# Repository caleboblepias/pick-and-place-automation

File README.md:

# pick-and-place-automation
This project implements the embedded control backbone of an automated pick and place machine. The system centers on a custom STM32F103RB-based PCB running bare-metal firmware for precise motion control of stepper and servo actuators.

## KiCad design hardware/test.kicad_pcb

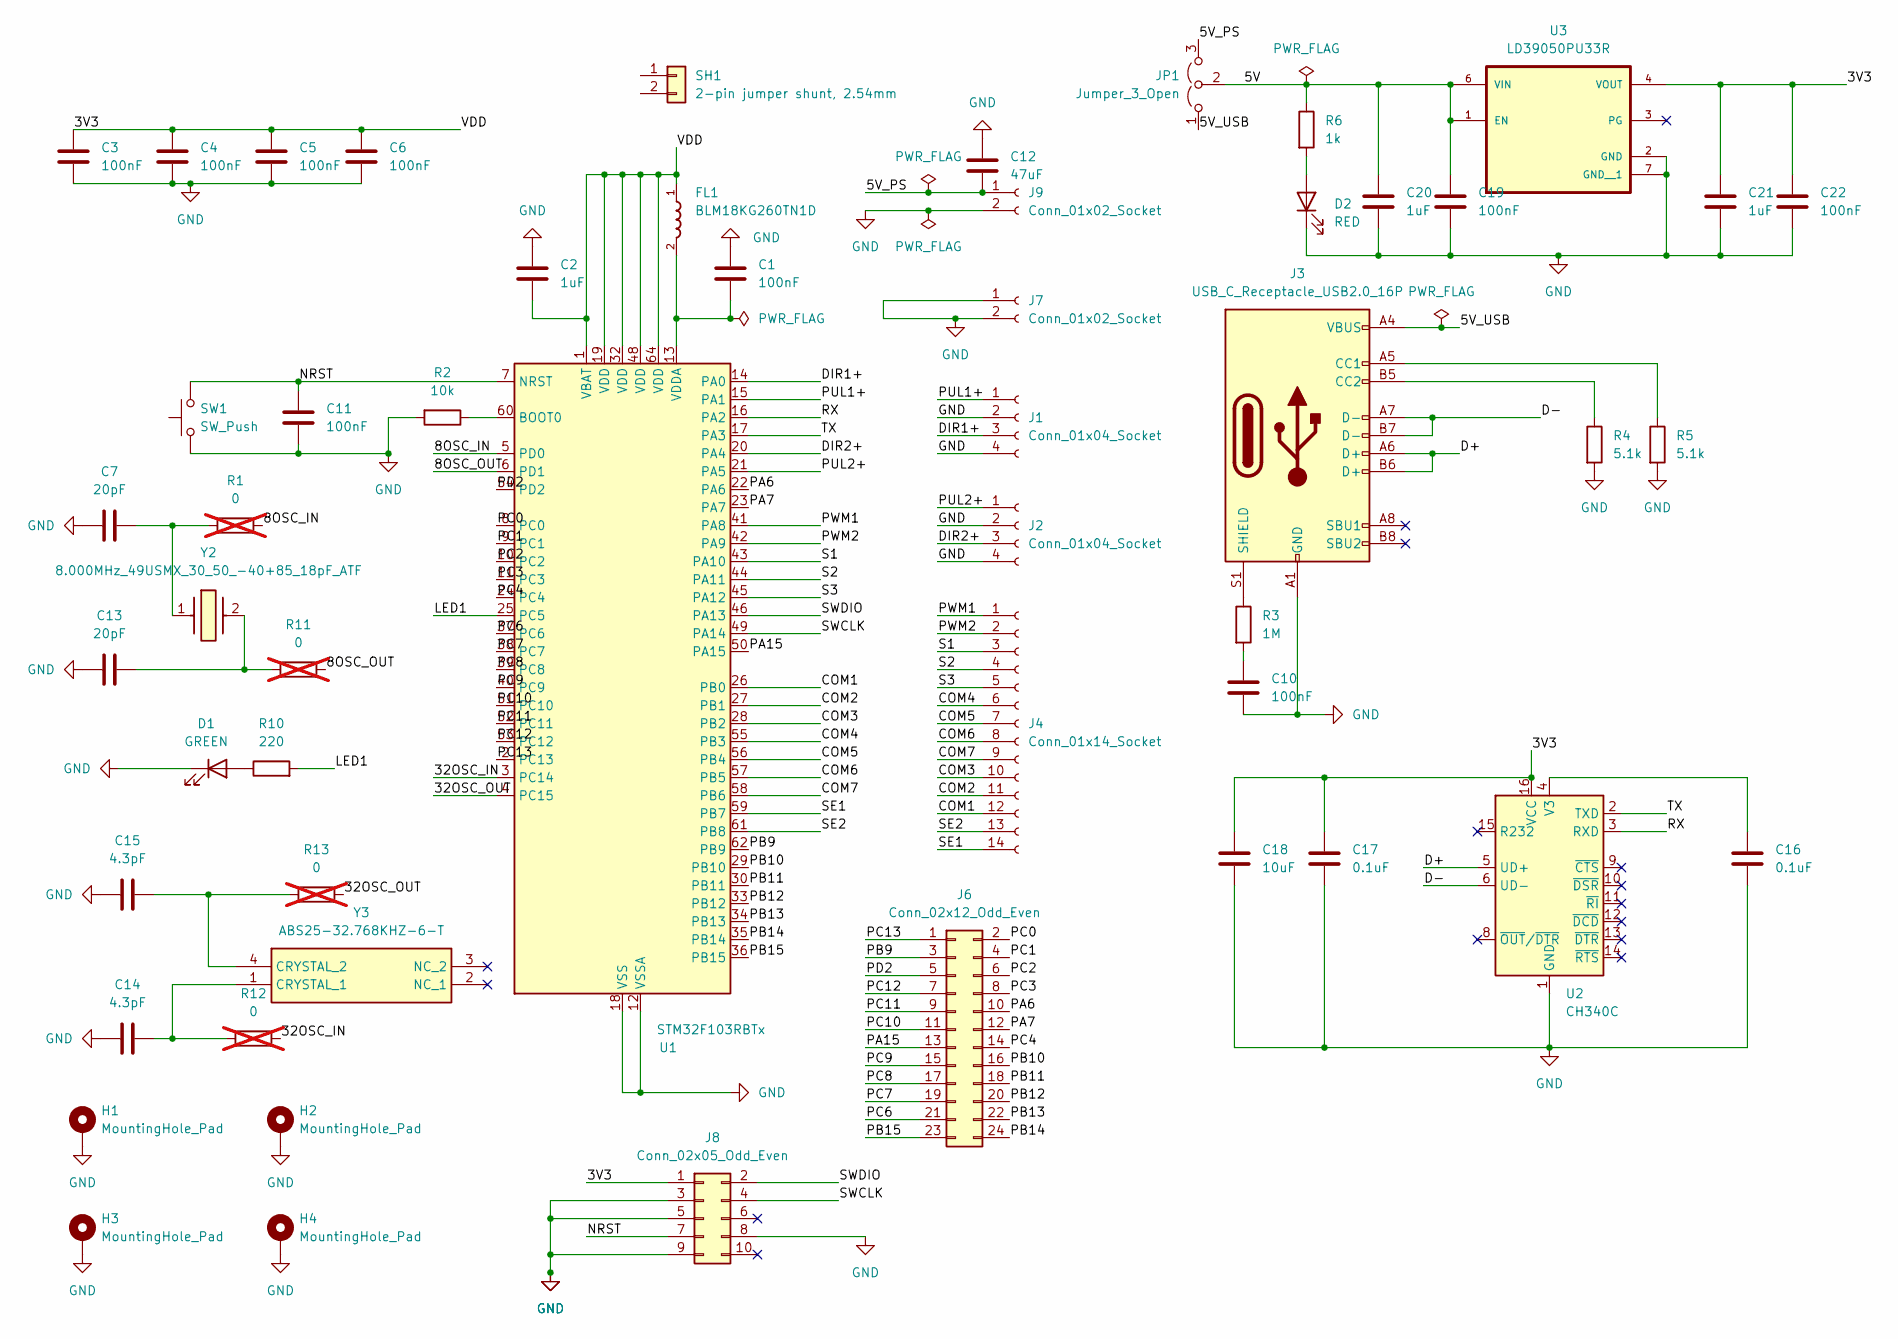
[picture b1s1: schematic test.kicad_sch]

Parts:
C1, C3, C4, C5, C6, C10, C11, C19, C22: 100nF; C_0603_1608Metric
C2, C20, C21: 1uF; C_0603_1608Metric
C7, C13: 20pF; C_0603_1608Metric
C12: 47uF; C_1210_3225Metric
C14, C15: 4.3pF; C_0603_1608Metric
C16, C17: 0.1uF; C_0603_1608Metric
C18: 10uF; C_0603_1608Metric
D1: GREEN; LED_0603_1608Metric
D2: RED; LED_0603_1608Metric
FL1: BLM18KG260TN1D; BEADC1608X75N
H1, H2, H3, H4: MountingHole_Pad; MountingHole_3.2mm_M3_Pad
J1, J2: Conn_01x04_Socket; PhoenixContact_MC_1,5_4-G-3.5_1x04_P3.50mm_Horizontal
J3: USB_C_Receptacle_USB2.0_16P; USB_C_Receptacle_HRO_TYPE-C-31-M-12
J4: Conn_01x14_Socket; PhoenixContact_MC_1,5_14-G-3.5_1x14_P3.50mm_Horizontal
J6: Conn_02x12_Odd_Even; PinHeader_2x12_P2.54mm_Vertical
J7, J9: Conn_01x02_Socket; PhoenixContact_MC_1,5_2-G-3.5_1x02_P3.50mm_Horizontal
J8: Conn_02x05_Odd_Even; PinHeader_2x05_P2.54mm_Vertical
JP1: Jumper_3_Open; PinHeader_1x03_P2.54mm_Vertical
R1, R11, R12, R13: 0; R_0603_1608Metric; not fitted
R2: 10k; R_0603_1608Metric
R3: 1M; R_0603_1608Metric
R4, R5: 5.1k; R_0603_1608Metric
R6: 1k; R_0603_1608Metric
R10: 220; R_0603_1608Metric
SH1: 2-pin jumper shunt, 2.54mm
SW1: SW_Push; SW_SPST_TL3342
U1: STM32F103RBTx; LQFP-64_10x10mm_P0.5mm
U2: CH340C; SOIC-16_3.9x9.9mm_P1.27mm
U3: LD39050PU33R; SON95P300X300X100-7N; DIGI-KEY_PART_NUMBER 497-8716-1-ND
Y2: 8.000MHz_49USMX_30_50_-40+85_18pF_ATF; 8000MHz49USMX3050408518pFATF; Manufacturer_Part_Number 8.000MHz 49USMX/30/50/-40+85/18pF/ATF
Y3: ABS25-32.768KHZ-6-T; ABS2532768KHZT; Manufacturer_Part_Number ABS25-32.768KHZ-6-T

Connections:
/3V3: C2.2, C3.1, C4.1, C5.1, C6.1, C17.1, C18.1, C21.1, C22.1, FL1.1, J8.1, U1.1 (VBAT), U1.19 (VDD), U1.32 (VDD), U1.48 (VDD), U1.64 (VDD), U2.16 (VCC), U3.4 (VOUT)
/5V: C19.1, C20.1, JP1.2 (C), R6.1, U3.1 (EN), U3.6 (VIN)
/5V_PS: C12.2, J9.1, JP1.3 (B)
/5V_USB: J3.A4 (VBUS), J3.A9 (VBUS), J3.B4 (VBUS), J3.B9 (VBUS), JP1.1 (A)
/8OSC_IN: R1.2, U1.5 (PD0)
/8OSC_OUT: R11.2, U1.6 (PD1)
/32OSC_IN: R12.2, U1.3 (PC14)
/32OSC_OUT: R13.2, U1.4 (PC15)
/COM1: J4.12, U1.26 (PB0)
/COM2: J4.11, U1.27 (PB1)
/COM3: J4.10, U1.28 (PB2)
/COM4: J4.6, U1.55 (PB3)
/COM5: J4.7, U1.56 (PB4)
/COM6: J4.8, U1.57 (PB5)
/COM7: J4.9, U1.58 (PB6)
/D+: J3.A6 (D+), J3.B6 (D+), U2.5 (UD+)
/D-: J3.A7 (D-), J3.B7 (D-), U2.6 (UD-)
/DIR1+: J1.3, U1.14 (PA0)
/DIR2+: J2.3, U1.20 (PA4)
/LED1: R10.2, U1.25 (PC5)
/NRST: C11.1, J8.7, SW1.2, U1.7 (NRST)
/PA6: J6.10, U1.22 (PA6)
/PA7: J6.12, U1.23 (PA7)
/PA15: J6.13, U1.50 (PA15)
/PB9: J6.3, U1.62 (PB9)
/PB10: J6.16, U1.29 (PB10)
/PB11: J6.18, U1.30 (PB11)
/PB12: J6.20, U1.33 (PB12)
/PB13: J6.22, U1.34 (PB13)
/PB14: J6.24, U1.35 (PB14)
/PB15: J6.23, U1.36 (PB15)
/PC0: J6.2, U1.8 (PC0)
/PC1: J6.4, U1.9 (PC1)
/PC2: J6.6, U1.10 (PC2)
/PC3: J6.8, U1.11 (PC3)
/PC4: J6.14, U1.24 (PC4)
/PC6: J6.21, U1.37 (PC6)
/PC7: J6.19, U1.38 (PC7)
/PC8: J6.17, U1.39 (PC8)
/PC9: J6.15, U1.40 (PC9)
/PC10: J6.11, U1.51 (PC10)
/PC11: J6.9, U1.52 (PC11)
/PC12: J6.7, U1.53 (PC12)
/PC13: J6.1, U1.2 (PC13)
/PD2: J6.5, U1.54 (PD2)
/PUL1+: J1.1, U1.15 (PA1)
/PUL2+: J2.1, U1.21 (PA5)
/PWM1: J4.1, U1.41 (PA8)
/PWM2: J4.2, U1.42 (PA9)
/RX: U1.16 (PA2), U2.3 (RXD)
/S1: J4.3, U1.43 (PA10)
/S2: J4.4, U1.44 (PA11)
/S3: J4.5, U1.45 (PA12)
/SE1: J4.14, U1.59 (PB7)
/SE2: J4.13, U1.61 (PB8)
/SWCLK: J8.4, U1.49 (PA14)
/SWDIO: J8.2, U1.46 (PA13)
/TX: U1.17 (PA3), U2.2 (TXD)
GND: C1.1, C2.1, C3.2, C4.2, C5.2, C6.2, C7.1, C10.2, C11.2, C12.1, C13.2, C14.1, C15.2, C16.2, C17.2, C18.2, C19.2, C20.2, C21.2, C22.2, D1.1 (K), D2.1 (K), H1.1, H2.1, H3.1, H4.1, J1.2, J1.4, J2.2, J2.4, J3.A1 (GND), J3.A12 (GND), J3.B1 (GND), J3.B12 (GND), J7.1, J7.2, J8.3, J8.5, J8.8, J8.9, J9.2, R2.2, R4.2, R5.2, SW1.1, U1.12 (VSSA), U1.18 (VSS), U1.31 (VSS), U1.47 (VSS), U1.63 (VSS), U2.1 (GND), U3.2 (GND), U3.7 (GND__1)
unnamed: C7.2, R1.1, Y2.1
unnamed: C10.1, R3.2
unnamed: C13.1, R11.1, Y2.2
unnamed: D1.2 (A), R10.1
unnamed: D2.2 (A), R6.2
unnamed: J3.A5 (CC1), R5.1
unnamed: J3.B5 (CC2), R4.1
unnamed: J3.S1 (SHIELD), R3.1
unnamed: R2.1, U1.60 (BOOT0)
unnamed: C1.2, FL1.2, U1.13 (VDDA)
unnamed: C16.1, U2.4 (V3)
unnamed: C14.2, R12.1, Y3.1 (CRYSTAL_1)
unnamed: C15.1, R13.1, Y3.4 (CRYSTAL_2)

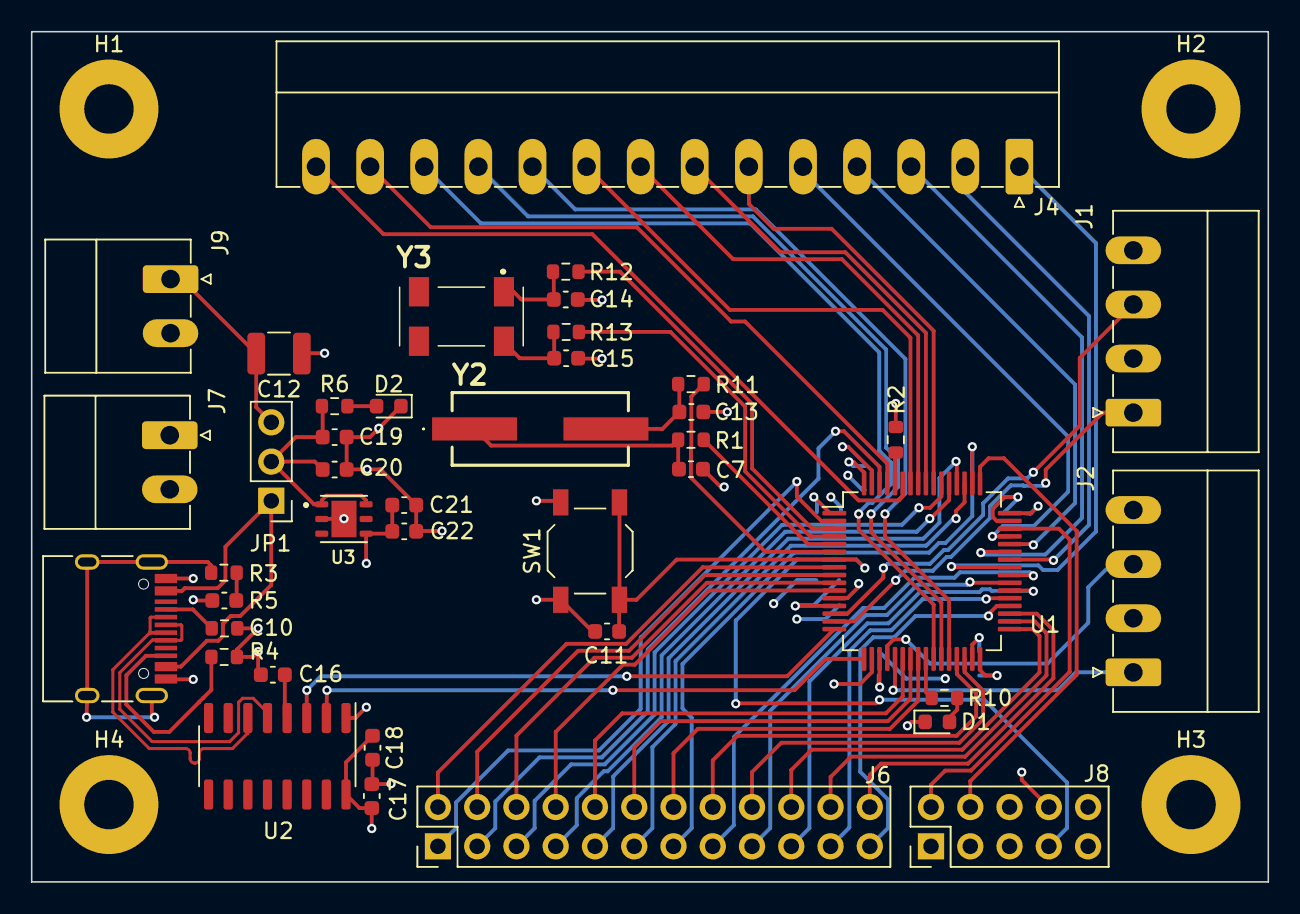
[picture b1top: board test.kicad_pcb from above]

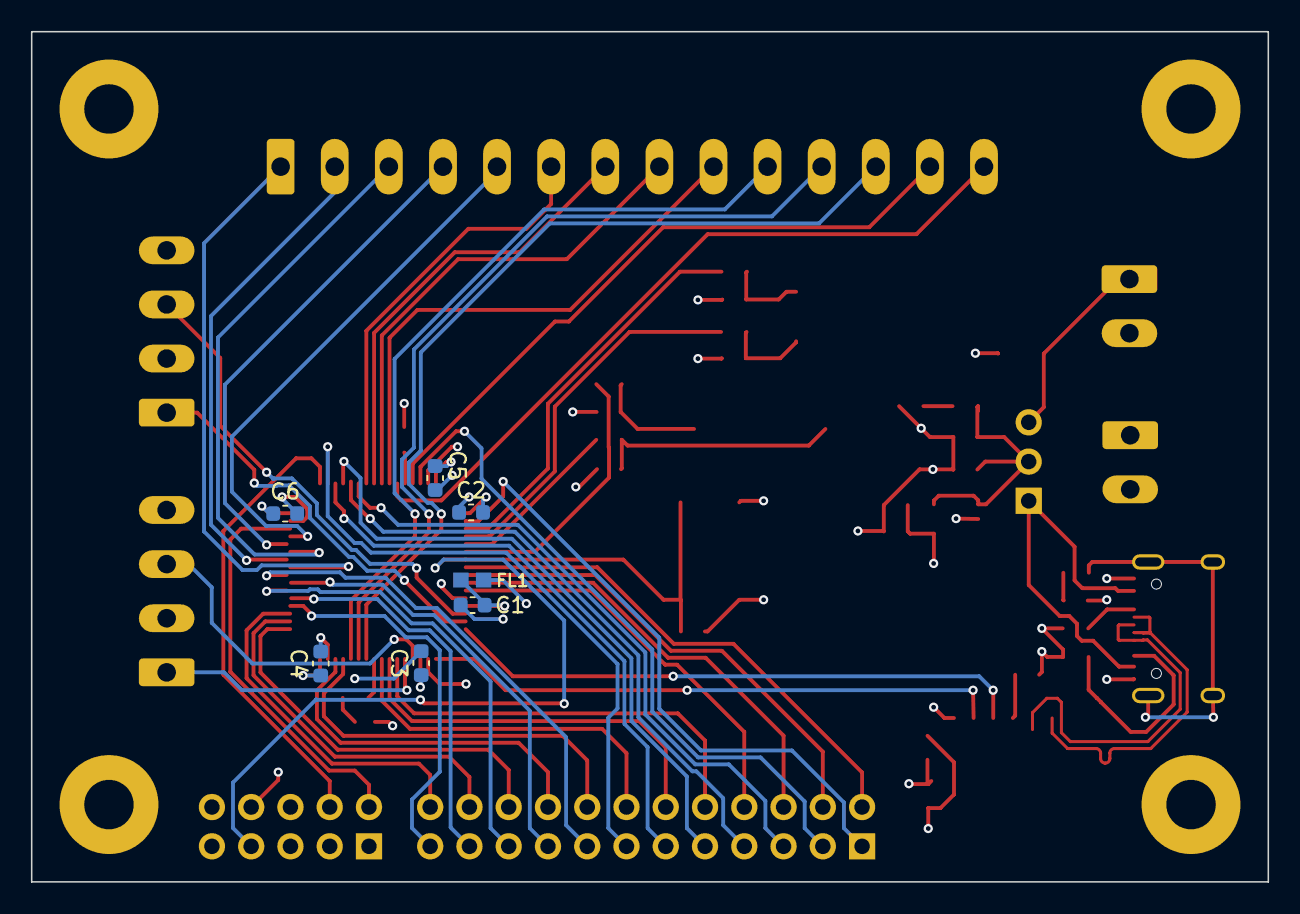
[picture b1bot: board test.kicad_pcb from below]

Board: 4 copper layers, 80.0 x 55.0 mm, 52 parts (7 on the bottom side), 72 nets.

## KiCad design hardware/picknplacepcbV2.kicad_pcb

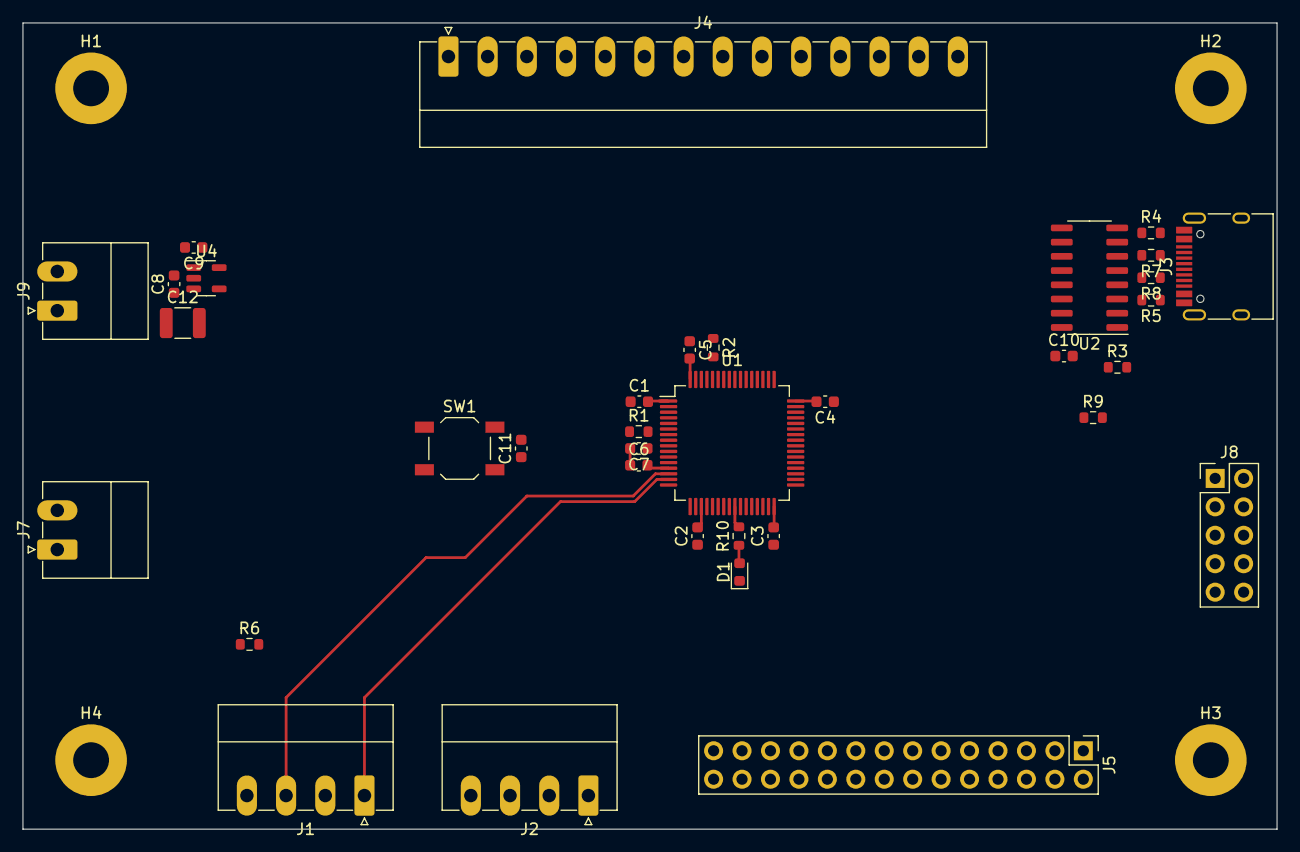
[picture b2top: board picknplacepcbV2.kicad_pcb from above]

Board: 2 copper layers, 112.0 x 72.0 mm, 39 parts (0 on the bottom side), 68 nets.

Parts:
C1, C2, C3, C4, C5, C6: 0.1uF; C_0603_1608Metric
C7, C8, C9: 1uF; C_0603_1608Metric
C10, C11: 100nF; C_0603_1608Metric
C12: 47uF; C_1210_3225Metric
D1: LED; LED_0603_1608Metric
H1, H2, H3, H4: MountingHole_Pad; MountingHole_3.2mm_M3_Pad
J1, J2: Conn_01x04_Socket; PhoenixContact_MC_1,5_4-G-3.5_1x04_P3.50mm_Horizontal
J3: USB_C_Receptacle_USB2.0_16P; USB_C_Receptacle_HRO_TYPE-C-31-M-12
J4: Conn_01x14_Socket; PhoenixContact_MC_1,5_14-G-3.5_1x14_P3.50mm_Horizontal
J5: Conn_02x14_Odd_Even; PinHeader_2x14_P2.54mm_Vertical
J7, J9: Conn_01x02_Socket; PhoenixContact_MC_1,5_2-G-3.5_1x02_P3.50mm_Horizontal
J8: Conn_02x05_Odd_Even; PinHeader_2x05_P2.54mm_Vertical
R1, R2: 10k; R_0603_1608Metric
R3: 1M; R_0603_1608Metric
R4, R5: 5.1k; R_0603_1608Metric
R6: 0; R_0603_1608Metric
R7, R8: 22; R_0603_1608Metric
R9: 100; R_0603_1608Metric
R10: 220; R_0603_1608Metric
SW1: SW_Push; SW_SPST_TL3342
U1: STM32F103RBTx; LQFP-64_10x10mm_P0.5mm
U2: CH340C; SOIC-16_3.9x9.9mm_P1.27mm
U4: AP2112K-3.3; SOT-23-5

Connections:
+5V: C8.1, C12.2, J3.A4 (VBUS), J3.A9 (VBUS), J3.B4 (VBUS), J3.B9 (VBUS), J9.1, U4.1 (VIN), U4.3 (EN)
/+3.3V: C1.2, C2.2, C3.2, C4.2, C5.2, C6.2, C9.1, R1.2, R9.1, U1.1 (VBAT), U1.13 (VDDA), U1.19 (VDD), U1.32 (VDD), U1.48 (VDD), U1.64 (VDD), U2.16 (VCC), U4.5 (VOUT)
/+3.3V_SENSE: J8.1, R9.2
/COM1: J4.3, U1.26 (PB0)
/COM2: J4.4, U1.27 (PB1)
/COM3: J4.5, U1.28 (PB2)
/COM4: J4.6, U1.55 (PB3)
/COM5: J4.7, U1.56 (PB4)
/COM6: J4.8, U1.57 (PB5)
/COM7: J4.9, U1.58 (PB6)
/D+: R8.2, U2.5 (UD+)
/D-: R7.2, U2.6 (UD-)
/DIR1+: J1.3, U1.14 (PA0)
/DIR2+: J2.3, U1.20 (PA4)
/GND_EXT: J7.1, R6.1
/LED1: R10.2, U1.25 (PC5)
/NRST: C11.1, J8.7, R1.1, SW1.2, U1.7 (NRST)
/PA6: J5.10, U1.22 (PA6)
/PA7: J5.12, U1.23 (PA7)
/PA15: J5.14, U1.50 (PA15)
/PB9: J5.16, U1.62 (PB9)
/PB10: J5.18, U1.29 (PB10)
/PB11: J5.20, U1.30 (PB11)
/PB12: J5.22, U1.33 (PB12)
/PB13: J5.24, U1.34 (PB13)
/PB14: J5.26, U1.35 (PB14)
/PB15: J5.28, U1.36 (PB15)
/PC0: J5.7, U1.8 (PC0)
/PC1: J5.9, U1.9 (PC1)
/PC2: J5.11, U1.10 (PC2)
/PC3: J5.13, U1.11 (PC3)
/PC4: J5.15, U1.24 (PC4)
/PC6: J5.17, U1.37 (PC6)
/PC7: J5.19, U1.38 (PC7)
/PC8: J5.21, U1.39 (PC8)
/PC9: J5.23, U1.40 (PC9)
/PC10: J5.25, U1.51 (PC10)
/PC11: J5.27, U1.52 (PC11)
/PC12: J5.2, U1.53 (PC12)
/PC13: J5.4, U1.2 (PC13)
/PC14: J5.6, U1.3 (PC14)
/PC15: J5.8, U1.4 (PC15)
/PD0: J5.1, U1.5 (PD0)
/PD1: J5.3, U1.6 (PD1)
/PD2: J5.5, U1.54 (PD2)
/PUL1+: J1.1, U1.15 (PA1)
/PUL2+: J2.1, U1.21 (PA5)
/PWM1: J4.1, U1.41 (PA8)
/PWM2: J4.2, U1.42 (PA9)
/RX: U1.16 (PA2), U2.3 (RXD)
/S1: J4.10, U1.43 (PA10)
/S2: J4.11, U1.44 (PA11)
/S3: J4.12, U1.45 (PA12)
/SE1: J4.13, U1.59 (PB7)
/SE2: J4.14, U1.61 (PB8)
/SWCLK: J8.4, U1.49 (PA14)
/SWDIO: J8.2, U1.46 (PA13)
/TX: U1.17 (PA3), U2.2 (TXD)
GND: C1.1, C2.1, C3.1, C4.1, C5.1, C7.1, C8.2, C9.2, C10.2, C11.2, C12.1, D1.1 (K), H1.1, H2.1, H3.1, H4.1, J1.2, J1.4, J2.2, J2.4, J3.A1 (GND), J3.A12 (GND), J3.B1 (GND), J3.B12 (GND), J7.2, J8.3, J8.5, J8.8, J8.9, J9.2, R2.1, R4.2, R5.2, R6.2, SW1.1, U1.12 (VSSA), U1.18 (VSS), U1.31 (VSS), U1.47 (VSS), U1.63 (VSS), U2.1 (GND), U4.2 (GND)
unnamed: C6.1, C7.2
unnamed: C10.1, R3.2
unnamed: D1.2 (A), R10.1
unnamed: J3.A5 (CC1), R5.1
unnamed: J3.B5 (CC2), R4.1
unnamed: J3.A6 (D+), J3.B6 (D+), R8.1
unnamed: J3.A7 (D-), J3.B7 (D-), R7.1
unnamed: J3.S1 (SHIELD), R3.1
unnamed: R2.2, U1.60 (BOOT0)

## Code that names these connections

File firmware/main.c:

#include <stdint.h>     // Brings in fixed-width types: uint8_t, uint16_t, etc.
#include "stm32f10x.h"
#include "uart.h"
#include "stepper.h"
#include "gpio.h"
#include "servo.h"
#include "system.h"
#include "calibrate.h"
#include "limit.h"

int main(void)
{
	set_system_state(IDLE);
	USART2_init();
	
	limit_init(0); // Y top limit at PB0
	limit_init(1); // Y bottom limit at PB1
	limit_init(2); // Z top limit at PB2
	limit_init(3); // Z bottom limit at PB3
	
	
	pulse_width_init();
	
	stepper1_init();
	stepper2_init();
	
	set_stepper1_step_freq(6400);
	set_stepper2_step_freq(6400);
	
	set_stepper1_dir(1);
	set_stepper2_dir(0);
	
	//drive_stepper1(800);
	//drive_stepper2(800);
	//calibrate();
	
	servo1_init();
	set_servo1_angle(135);
	/*
	for (uint32_t i = 0; i < 8000; i++) {}
	set_servo1_angle(135);
	for (uint32_t i = 0; i < 8000; i++) {}
	set_servo1_angle(270);
	for (uint32_t i = 0; i < 8000; i++) {}
	set_servo1_angle(135);
	for (uint32_t i = 0; i < 8000; i++) {}
	set_servo1_angle(270);
	*/
	
	//GPIO_init_pud_input(GPIOA, 4);
	
	//servo1_init();
	
	/*
	//set_servo1_angle(90);
	set_servo1_angle(0);
	for(uint32_t i = 0; i < (1000 * 8000); ++i) __asm__("nop");
	set_servo1_angle(135);
	for(uint32_t i = 0; i < (1000 * 8000); ++i) __asm__("nop");
	set_servo1_angle(270);
	for(uint32_t i = 0; i < (1000 * 8000); ++i) __asm__("nop");
	for(uint32_t i = 0; i < 270; ++i) {
		set_servo1_angle(i++);
		for(uint32_t j = 0; j < (100 * 8000); ++j) __asm__("nop");
	}
	set_servo1_angle(0);
	*/
	while(1)
	{
			
		
		/*
		if (!(GPIO_read_IDR(GPIOA, 4))) {
			drive_stepper1(10);
		}
		*/
		
		/*
		if (get_packet_ready()) {
			const volatile uint8_t* rx_buffer = get_rx_buffer();
			uint8_t opcode = rx_buffer[0];
			uint8_t len = rx_buffer[1];

			USART2_write(0xAA);
			USART2_write(opcode);
			USART2_write(len);
			for (uint8_t i = 0; i < len; ++i)
				USART2_write(rx_buffer[2 + i]);
			USART2_write(rx_buffer[2 + len]);  
			USART2_write(0x55);

			set_packet_ready(0);               
		}
		*/
		
		// main handler
		if (get_packet_ready() && get_system_state() == IDLE) {
			const volatile uint8_t* rx_buffer = get_rx_buffer();
			uint8_t opcode = rx_buffer[0];
			uint8_t len = rx_buffer[1];
			
			switch(opcode) {
				
				// 0x01: drive stepper 1
				case 0x01:
					if (len > 1) {
						uint8_t dir = rx_buffer[2];
						uint32_t steps = 0;
						/*
						for (uint8_t i = 0; i < len; ++i) {
							steps += rx_buffer[3 + i];
						}
						*/
						for (uint8_t i = 0; i < len - 1; ++i) { // len = 3, 1 dir + 2 step bytes
							steps |= ((uint32_t)rx_buffer[3 + i]) << (8 * i);
						}


						set_stepper1_dir(dir);
						drive_stepper1(steps);
						set_system_state(RUNNING);
						//USART2_write(0x01);
					}
					set_packet_ready(0);
					//USART2_send_ack();
					break;
					
				// 0x02: drive stepper 2
				case 0x02:
					if (len > 1) {
						uint8_t dir = rx_buffer[2];
						uint32_t steps = 0;
						/*
						for (uint8_t i = 0; i < len; ++i) {
							steps += rx_buffer[3 + i];
						}
						*/
						for (uint8_t i = 0; i < len - 1; ++i) { // len = 3, 1 dir + 2 step bytes
							steps |= ((uint32_t)rx_buffer[3 + i]) << (8 * i);
						}
						set_stepper2_dir(dir);
						drive_stepper2(steps);
						set_system_state(RUNNING);
						//USART2_write(0x02);
					}
					set_packet_ready(0);
					//USART2_send_ack();
					break;
			
				// 0x03: set wrist angle
				case 0x03:
					if (len == 1) {
						uint8_t angle = rx_buffer[2];
						set_servo1_angle(angle);
						USART2_write(0x03);
					}
					set_packet_ready(0);
					USART2_send_ack();
					break;
					
					
				// 0x04: set grabber angle
				case 0x04:
					if (len == 1) {
						uint8_t angle = rx_buffer[2];
						set_servo2_angle(angle);
						USART2_write(0x04);
					}
					set_packet_ready(0);
					USART2_send_ack();
					break;
					
				
				case 0x10:
					set_packet_ready(0);
					
					calibrate();
					break;	
					
				default:
					USART2_write(0x00);
					USART2_send_nack();
					break;
				
				
				
			
			
			
			
			
			
			}
			
			
		}
		
		
	}
}

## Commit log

2025-09-02 add firmware and hardware folders
2025-09-02 removed pdfs
2025-09-02 added board image
2025-09-02 updated gitignore
